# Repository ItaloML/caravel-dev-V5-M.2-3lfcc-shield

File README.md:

# caravel-dev-V5-M.2-3lfcc-shield
Repository for the files of a testing Borad for the 3lfcc project (caravan harness). Due to a previous board for the testing setup being name Test Board the file names stayed like that.

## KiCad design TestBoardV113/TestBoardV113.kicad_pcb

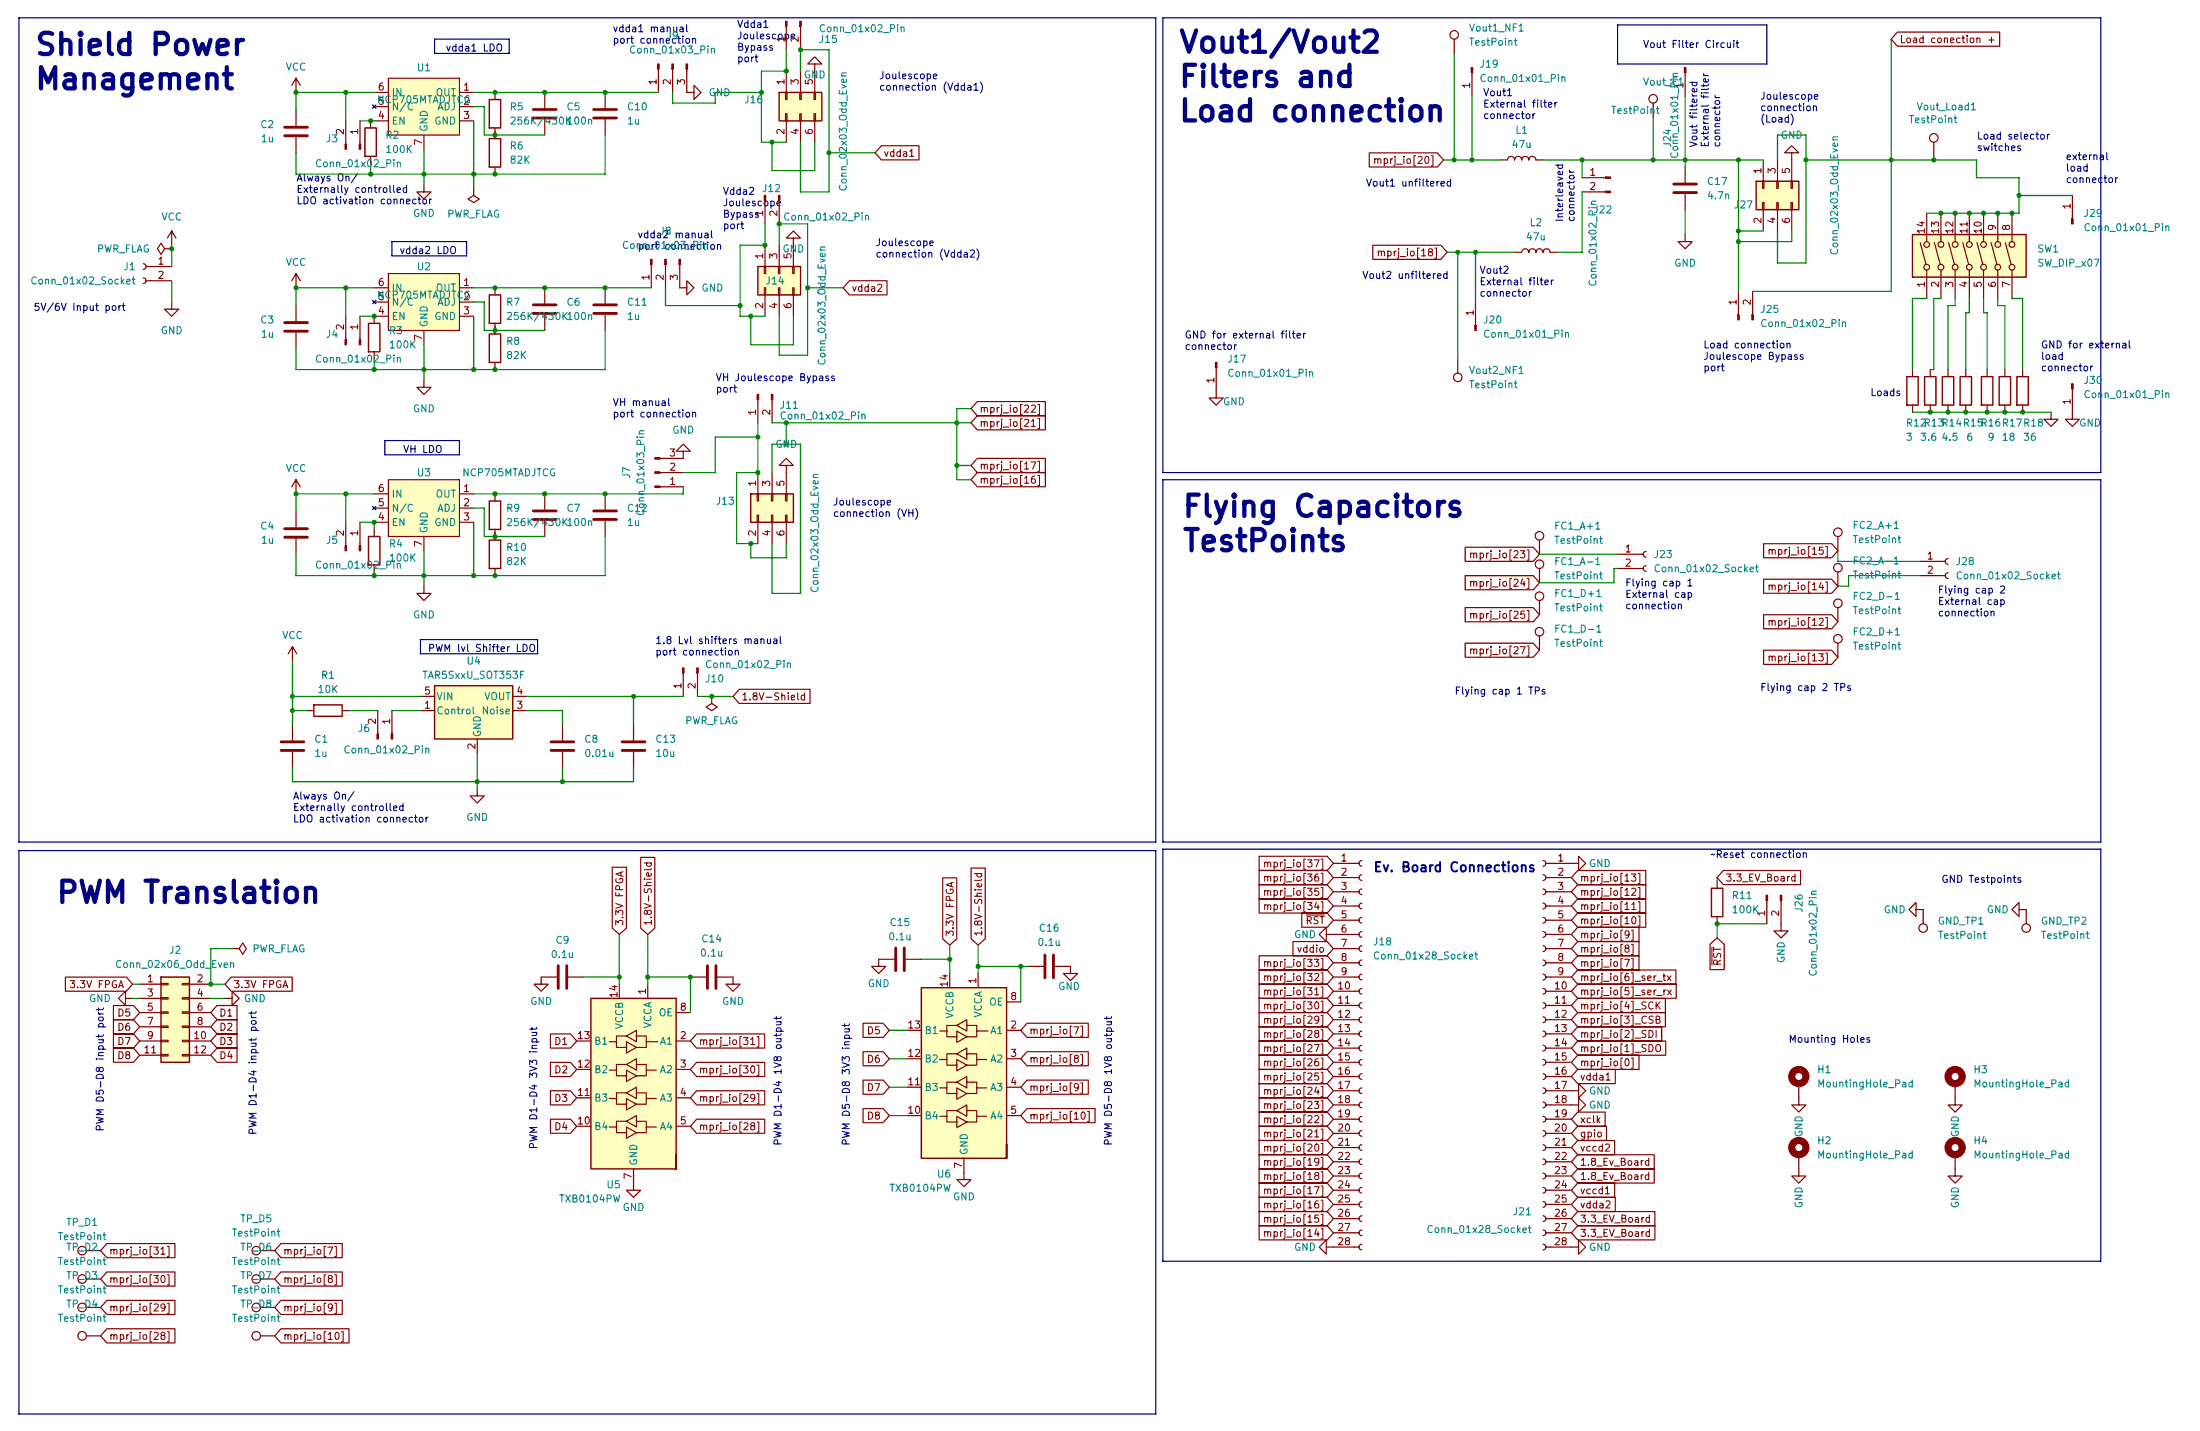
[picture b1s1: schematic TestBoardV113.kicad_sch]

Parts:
C1, C2, C3, C4, C10, C11, C12: 1u; C_0805_2012Metric
C5, C6, C7: 100n; C_0805_2012Metric
C8: 0.01u; C_0805_2012Metric
C9, C14, C15, C16: 0.1u; C_0805_2012Metric
C13: 10u; C_0805_2012Metric
C17: 4.7n; C_0805_2012Metric
FC1_A+1, FC1_A-1, FC1_D+1, FC1_D-1, FC2_A+1, FC2_A-1, FC2_D+1, FC2_D-1: TestPoint; TestPoint_Keystone_5019_Minature
GND_TP1, GND_TP2: TestPoint; TestPoint_Keystone_5019_Minature
H1, H2, H3, H4: MountingHole_Pad; MountingHole_3.2mm_M3_DIN965_Pad
J1: Conn_01x02_Socket; TerminalBlock_bornier-2_P5.08mm
J2: Conn_02x06_Odd_Even; PinHeader_2x06_P2.54mm_Vertical
J3, J4, J5, J6, J10, J11, J12, J15, J22, J25, J26: Conn_01x02_Pin; PinHeader_1x02_P2.54mm_Vertical
J7, J8, J9: Conn_01x03_Pin; PinHeader_1x03_P2.54mm_Vertical
J13, J14, J16, J27: Conn_02x03_Odd_Even; PinHeader_2x03_P2.54mm_Vertical
J17, J19, J20, J24, J29, J30: Conn_01x01_Pin; PinHeader_1x01_P2.54mm_Vertical
J18, J21: Conn_01x28_Socket; PinSocket_1x28_P2.54mm_Vertical
J23, J28: Conn_01x02_Socket; PinSocket_1x02_P2.54mm_Vertical
L1, L2: 47u; L_1210_3225Metric
R1: 10K; R_0805_2012Metric
R2, R3, R4, R11: 100K; R_0805_2012Metric
R5, R7, R9: 256K/430K; R_0805_2012Metric
R6, R8, R10: 82K; R_0805_2012Metric
R12: 3; R_2010_5025Metric
R13: 3.6; R_2010_5025Metric
R14: 4.5; R_2010_5025Metric
R15: 6; R_2010_5025Metric
R16: 9; R_2010_5025Metric
R17: 18; R_2010_5025Metric
R18: 36; R_2010_5025Metric
SW1: SW_DIP_x07; SW_DIP_SPSTx07_Slide_9.78x19.96mm_W7.62mm_P2.54mm
TP_D1, TP_D2, TP_D3, TP_D4, TP_D5, TP_D6, TP_D7, TP_D8: TestPoint; TestPoint_Keystone_5019_Minature
U1, U2, U3: NCP705MTADJTCG; DFN-6-1EP_2x2mm_P0.65mm_EP1.01x1.7mm
U4: TAR5SxxU_SOT353F; SOT-353F
U5, U6: TXB0104PW; TSSOP-14_4.4x5mm_P0.65mm
Vout1_NF1, Vout2_NF1: TestPoint; TestPoint_Keystone_5019_Minature
Vout_F1: TestPoint; TestPoint_Keystone_5019_Minature
Vout_Load1: TestPoint; TestPoint_Keystone_5019_Minature

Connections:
1.8V-Shield: C14.2, C16.2, J10.2, U5.1 (VCCA), U5.8 (OE), U6.1 (VCCA), U6.8 (OE)
1.8_Ev_Board: J21.22, J21.23
3.3V FPGA: C9.2, C15.2, J2.1, J2.2, U5.14 (VCCB), U6.14 (VCCB)
3.3_EV_Board: J21.26, J21.27, R11.1
D1: J2.6, U5.13 (B1)
D2: J2.8, U5.12 (B2)
D3: J2.10, U5.11 (B3)
D4: J2.12, U5.10 (B4)
D5: J2.5, U6.13 (B1)
D6: J2.7, U6.12 (B2)
D7: J2.9, U6.11 (B3)
D8: J2.11, U6.10 (B4)
GND: C1.2, C2.2, C3.2, C4.2, C8.2, C9.1, C10.2, C11.2, C12.2, C13.2, C14.1, C15.1, C16.1, C17.2, GND_TP1.1, GND_TP2.1, H1.1, H2.1, H3.1, H4.1, J1.2, J2.3, J2.4, J7.3, J8.3, J9.3, J13.5, J14.5, J16.5, J17.1, J18.6, J18.28, J21.1, J21.17, J21.18, J21.28, J26.2, J27.5, J30.1, R2.2, R3.2, R4.2, R6.2, R8.2, R10.2, R12.2, R13.2, R14.2, R15.2, R16.2, R17.2, R18.2, U1.3 (GND), U1.7 (GND), U2.3 (GND), U2.7 (GND), U3.3 (GND), U3.7 (GND), U4.2 (GND), U5.7 (GND), U6.7 (GND)
Load conection +: J25.2, J27.3, J27.4, J29.1, SW1.8, SW1.9, SW1.10, SW1.11, SW1.12, SW1.13, SW1.14, Vout_Load1.1
unnamed: J3.1, R2.1, U1.4 (EN)
unnamed: J4.1, R3.1, U2.4 (EN)
unnamed: J5.1, R4.1, U3.4 (EN)
unnamed: J6.1, U4.1 (Control)
unnamed: J6.2, R1.1
unnamed: C7.1, C12.1, J7.1, R9.1, U3.1 (OUT)
unnamed: C6.1, C11.1, J8.1, R7.1, U2.1 (OUT)
unnamed: C5.1, C10.1, J9.1, R5.1, U1.1 (OUT)
unnamed: C13.1, J10.1, U4.4 (VOUT)
unnamed: J7.2, J11.1, J13.1, J13.2, J13.6
unnamed: J8.2, J12.1, J14.1, J14.2, J14.6
unnamed: J9.2, J15.1, J16.1, J16.2, J16.6
unnamed: C17.1, J22.1, J24.1, J25.1, J27.1, J27.2, J27.6, L1.2, Vout_F1.1
unnamed: J22.2, L2.2
unnamed: R12.1, SW1.1
unnamed: R13.1, SW1.2
unnamed: R14.1, SW1.3
unnamed: R15.1, SW1.4
unnamed: R16.1, SW1.5
unnamed: R17.1, SW1.6
unnamed: R18.1, SW1.7
unnamed: C5.2, R5.2, R6.1, U1.2 (ADJ)
unnamed: C6.2, R7.2, R8.1, U2.2 (ADJ)
unnamed: C7.2, R9.2, R10.1, U3.2 (ADJ)
unnamed: C8.1, U4.3 (Noise)
VCC: C1.1, C2.1, C3.1, C4.1, J1.1, J3.2, J4.2, J5.2, R1.2, U1.6 (IN), U2.6 (IN), U3.6 (IN), U4.5 (VIN)
gpio: J21.20
mprj_io[0]: J21.15
mprj_io[1]_SDO: J21.14
mprj_io[2]_SDI: J21.13
mprj_io[3]_CSB: J21.12
mprj_io[4]_SCK: J21.11
mprj_io[5]_ser_rx: J21.10
mprj_io[6]_ser_tx: J21.9
mprj_io[7]: J21.8, TP_D5.1, U6.2 (A1)
mprj_io[8]: J21.7, TP_D6.1, U6.3 (A2)
mprj_io[9]: J21.6, TP_D7.1, U6.4 (A3)
mprj_io[10]: J21.5, TP_D8.1, U6.5 (A4)
mprj_io[11]: J21.4
mprj_io[12]: FC2_D-1.1, J21.3
mprj_io[13]: FC2_D+1.1, J21.2
mprj_io[14]: FC2_A-1.1, J18.27, J28.2
mprj_io[15]: FC2_A+1.1, J18.26, J28.1
mprj_io[16]: J11.2, J13.3, J13.4, J18.19, J18.20, J18.24, J18.25
mprj_io[18]: J18.23, J20.1, L2.1, Vout2_NF1.1
mprj_io[19]: J18.22
mprj_io[20]: J18.21, J19.1, L1.1, Vout1_NF1.1
mprj_io[23]: FC1_A+1.1, J18.18, J23.1
mprj_io[24]: FC1_A-1.1, J18.17, J23.2
mprj_io[25]: FC1_D+1.1, J18.16
mprj_io[26]: J18.15
mprj_io[27]: FC1_D-1.1, J18.14
mprj_io[28]: J18.13, TP_D4.1, U5.5 (A4)
mprj_io[29]: J18.12, TP_D3.1, U5.4 (A3)
mprj_io[30]: J18.11, TP_D2.1, U5.3 (A2)
mprj_io[31]: J18.10, TP_D1.1, U5.2 (A1)
mprj_io[32]: J18.9
mprj_io[33]: J18.8
mprj_io[34]: J18.4
mprj_io[35]: J18.3
mprj_io[36]: J18.2
mprj_io[37]: J18.1
vccd1: J21.24
vccd2: J21.21
vdda1: J15.2, J16.3, J16.4, J21.16
vdda2: J12.2, J14.3, J14.4, J21.25
vddio: J18.7
xclk: J21.19
~RST: J18.5, J26.1, R11.2

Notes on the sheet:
vdda2 LDO
PWM D1-D4 input port
Always On/ Externally controlled LDO activation connector
Shield Power Management
Vout filtered External filter connector
Mounting Holes
external load connector
PWM D1-D4 3V3 input
Vout2 External filter connector
Vout1 External filter connector
Vdda2 Joulescope Bypass port
PWM D5-D8 3V3 input
Loads
GND for external load connector
vdda1 LDO
vdda2 manual port connection
~Reset connection
Flying cap 1 TPs
Flying cap 2 TPs
Flying Capacitors TestPoints
Interleaved connector
Joulescope connection (Vdda1)
VH Joulescope Bypass port
PWM D1-D4 1V8 output
Flying cap 1 External cap connection
Load connection Joulescope Bypass port
Load selector switches
PWM D5-D8 1V8 output
Flying cap 2 External cap connection
GND for external filter connector
Vdda1 Joulescope Bypass port
PWM Translation
Vout2 unfiltered
VH manual port connection
PWM lvl Shifter LDO
PWM D5-D8 input port
Joulescope connection (Vdda2)
1.8 Lvl shifters manual port connection
Joulescope connection (VH)
Vout Filter Circuit

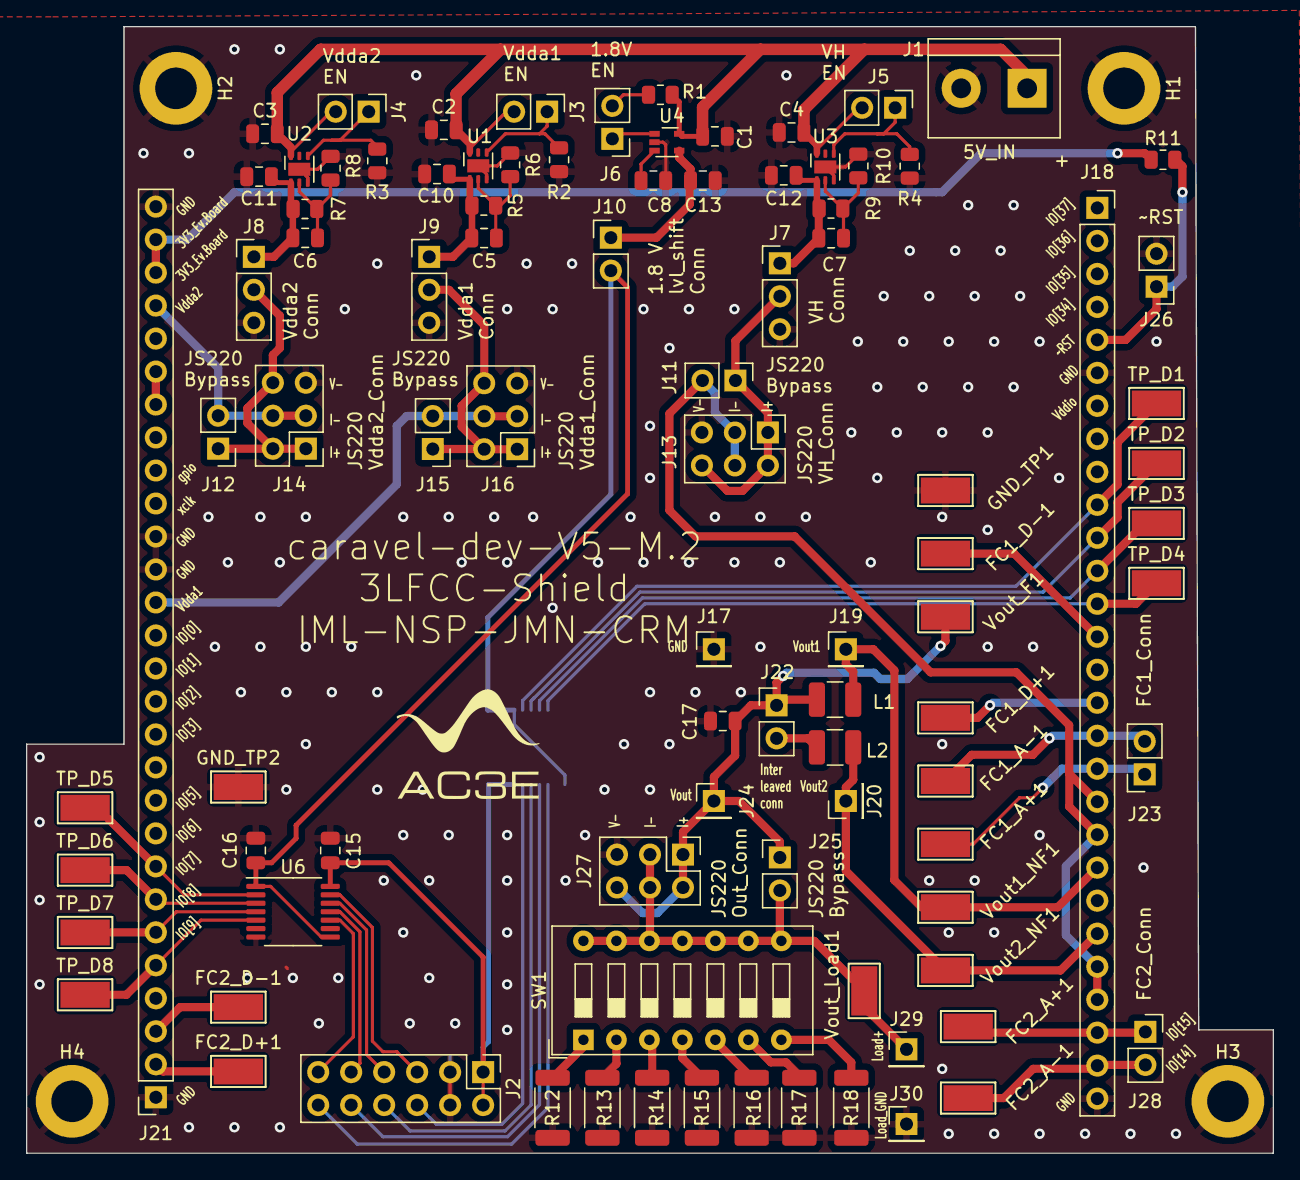
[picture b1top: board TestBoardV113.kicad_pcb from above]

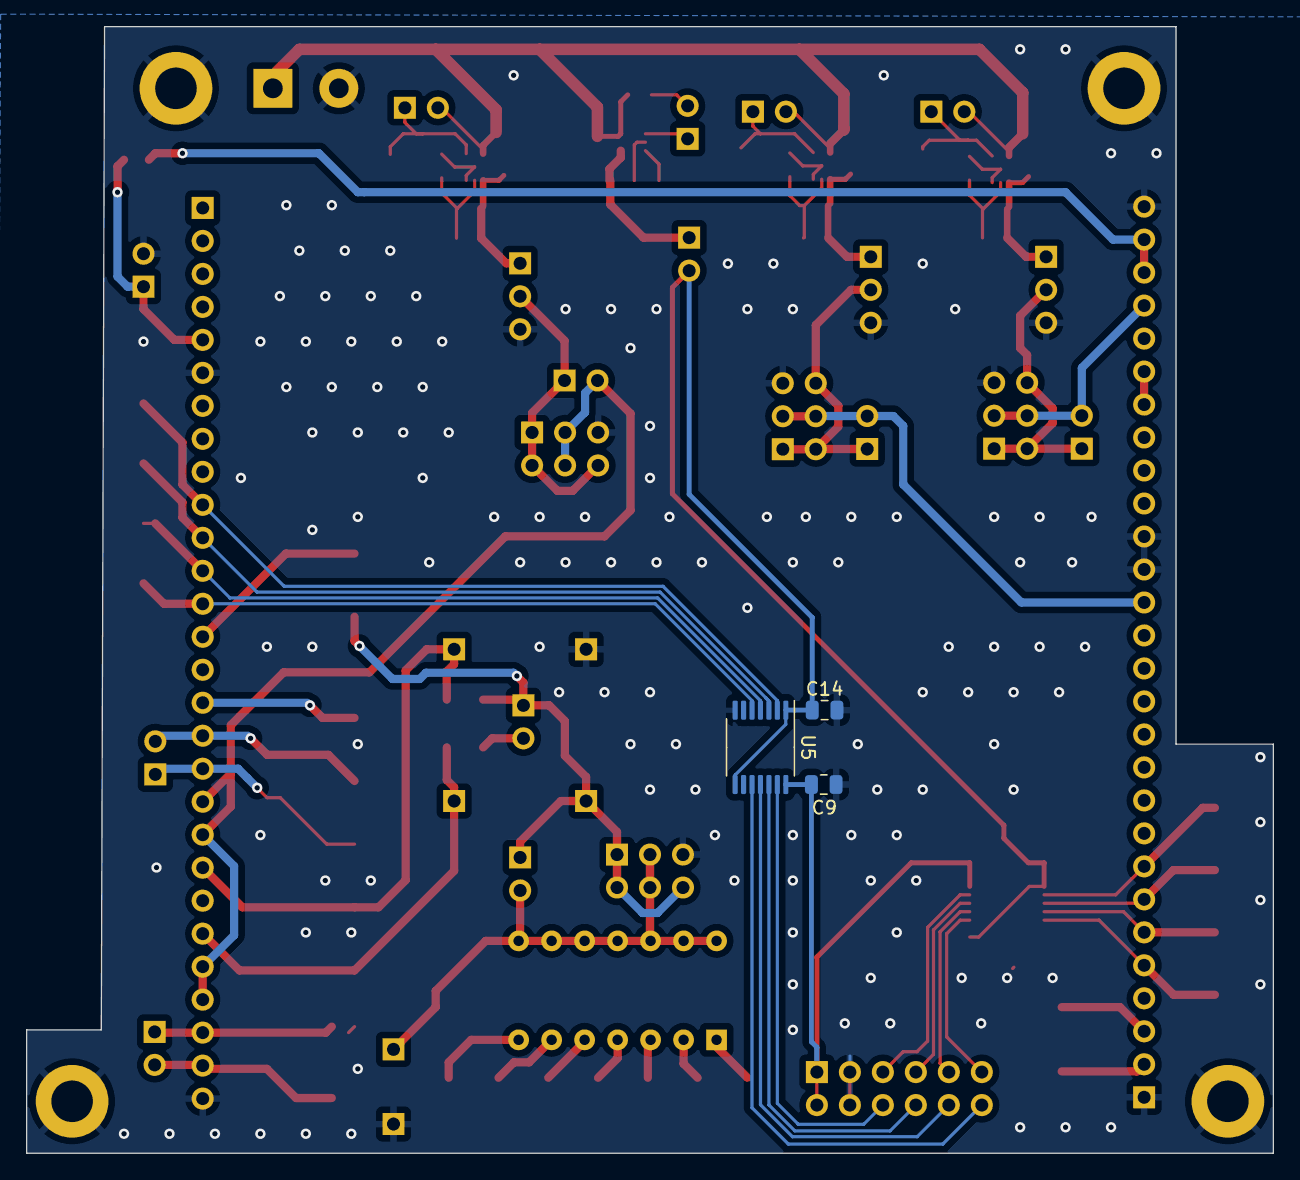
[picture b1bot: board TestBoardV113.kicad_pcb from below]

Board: 2 copper layers, 96.0 x 86.8 mm, 100 parts (3 on the bottom side), 62 nets.

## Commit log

2024-01-26 First Commit of files
    First Commit of the 3lfcc(TestBoard V1.1.3) files
2024-01-26 Added features
    Added Joulescope port for efficiency measurement with and without level shifters
2024-01-29 Changed Items
    Changed dip switch from 4
2024-01-29 Changed Items
    Added independent joulescope connection for vdda1 and 2, added testpoints for 1.8V pwm signals
2024-01-29 Minor errors
2024-01-29 Changes
    Test Resistors from 0805 to 2010
2024-01-30 Changes
    added real resistances values for the dip switch resistances and made the schematic more clear to read. Changed the fpga connector footprint for D1-D8 to avoid warnings
2024-01-31 Changes
    increased tracks width, change some component placements for better dynamic response, added a connection to ground for vdda1, vdda2 and VH
2024-01-31 pull up for ~reset
    Added pull-up resistor (100K) for ~Reset
2024-01-31 Changes
    Added labels
2024-01-31 saved
2024-01-31 new saved file
2024-01-31 Changed some names
2024-01-31 added external load connector
2024-01-31 size cchanges
2024-02-01 inductors size changed
